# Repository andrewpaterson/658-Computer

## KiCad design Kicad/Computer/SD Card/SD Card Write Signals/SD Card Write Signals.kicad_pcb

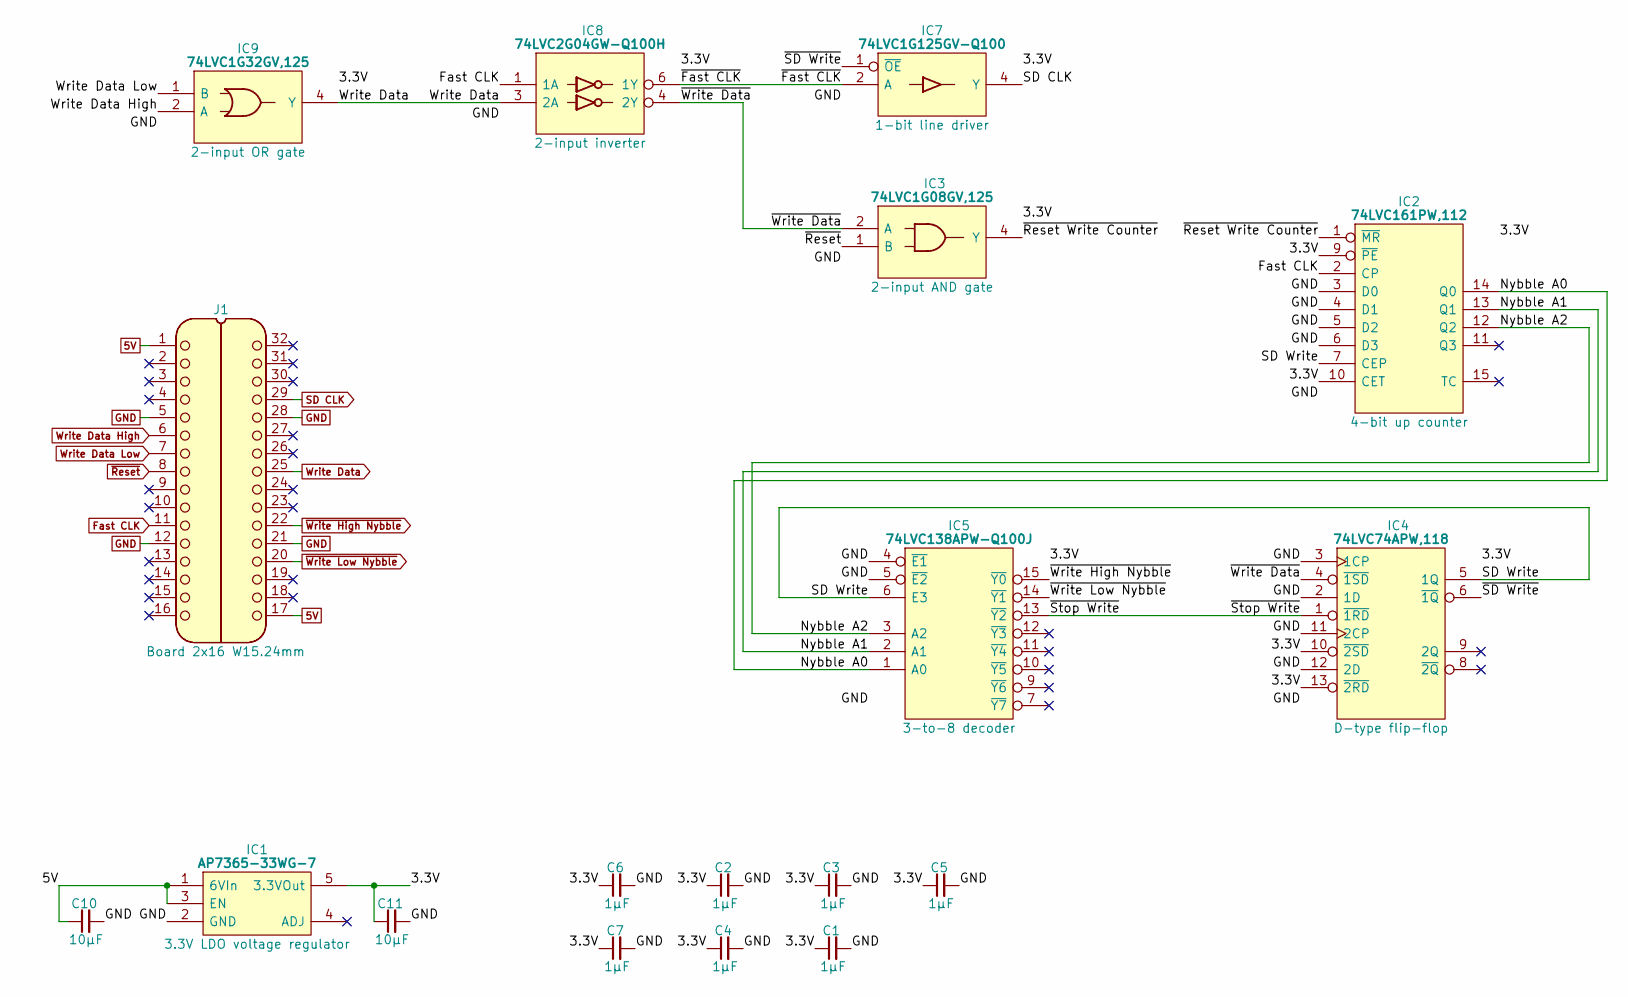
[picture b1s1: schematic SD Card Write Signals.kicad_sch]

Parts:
C1, C2, C3, C4, C5, C6, C7: 1μF; C_0805
C10, C11: 10μF; C_0805
IC1: AP7365-33WG-7; SOT95P285X130-5N; Manufacturer_Part_Number AP7365-33WG-7; Mouser Part Number 621-AP7365-33WG-7
IC2: 74LVC161PW,112; SOP65P640X110-16N; Mouser Part Number 771-LVC161PW112
IC3: 74LVC1G08GV,125; SOT95P275X110-5N; Manufacturer_Part_Number 74LVC1G08GV,125; Mouser Part Number 771-74LVC1G08GV
IC4: 74LVC74APW,118; SOP65P640X110-14N; Mouser Part Number 771-74LVC74APW-T
IC5: 74LVC138APW-Q100J; SOP65P640X110-16N; Mouser Part Number 771-74LVC138APWQ100J
IC7: 74LVC1G125GV-Q100; SOT95P275X110-5N; Mouser Part Number 771-74LVC1G125GVQ100
IC8: 74LVC2G04GW-Q100H; SOP65P210X110-6N; Manufacturer_Part_Number 74LVC2G04GW-Q100H; Mouser Part Number 771-74LVC2G04GWQ100H
IC9: 74LVC1G32GV,125; SOT95P275X110-5N; Manufacturer_Part_Number 74LVC1G32GV,125; Mouser Part Number 771-LVC1G32GV125
J1: Board 2x16 W15.24mm; DIP-32_Board_W15.24mm

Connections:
5V: C10.1, IC1.1 (6VIn), IC1.3 (EN), J1.1, J1.17
/3.3V: C1.1, C2.1, C3.1, C4.1, C5.1, C6.1, C7.1, C11.1, IC1.5 (3.3VOut), IC2.9 (~PE), IC2.10 (CET), IC2.16 (3V), IC3.5 (3V), IC4.10 (~2SD), IC4.13 (~2RD), IC4.14 (3V), IC5.16 (3V), IC7.5 (3V), IC8.5 (3V), IC9.5 (3V)
/Nybble A0: IC2.14 (Q0), IC5.1 (A0)
/Nybble A1: IC2.13 (Q1), IC5.2 (A1)
/Nybble A2: IC2.12 (Q2), IC5.3 (A2)
/SD Write: IC2.7 (CEP), IC4.5 (1Q), IC5.6 (E3)
/~Fast CLK: IC7.2 (A), IC8.6 (1Y)
/~Reset Write Counter: IC2.1 (~MR), IC3.4 (Y)
/~SD Write: IC4.6 (~1Q), IC7.1 (~OE)
/~Stop Write: IC4.1 (~1RD), IC5.13 (~Y2)
/~Write Data: IC3.2 (A), IC4.4 (~1SD), IC8.4 (2Y)
Fast CLK: IC2.2 (CP), IC8.1 (1A), J1.11
GND: C1.2, C2.2, C3.2, C4.2, C5.2, C6.2, C7.2, C10.2, C11.2, IC1.2 (GND), IC2.3 (D0), IC2.4 (D1), IC2.5 (D2), IC2.6 (D3), IC2.8 (GND), IC3.3 (GND), IC4.2 (1D), IC4.3 (1CP), IC4.7 (GND), IC4.11 (2CP), IC4.12 (2D), IC5.4 (~E1), IC5.5 (~E2), IC5.8 (GND), IC7.3 (GND), IC8.2 (GND), IC9.3 (GND), J1.5, J1.12, J1.21, J1.28
SD CLK: IC7.4 (Y), J1.29
Write Data: IC8.3 (2A), IC9.4 (Y), J1.25
Write Data High: IC9.2 (A), J1.6
Write Data Low: IC9.1 (B), J1.7
~Reset: IC3.1 (B), J1.8
~Write High Nybble: IC5.15 (~Y0), J1.22
~Write Low Nybble: IC5.14 (~Y1), J1.20

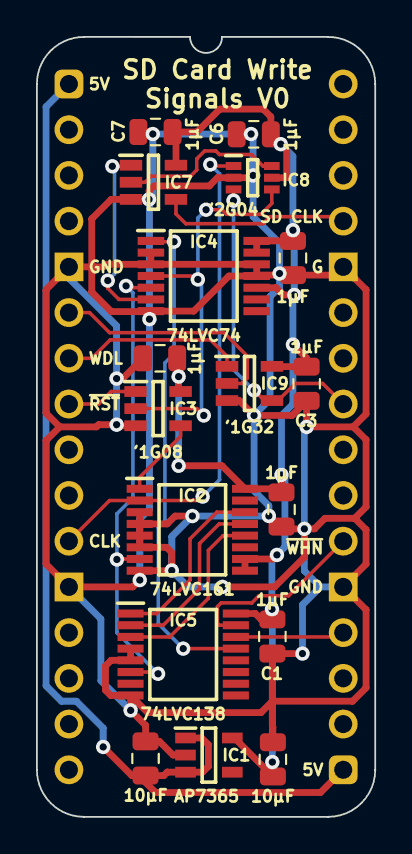
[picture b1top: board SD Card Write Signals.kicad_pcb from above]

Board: 2 copper layers, 18.8 x 43.3 mm, 18 parts (0 on the bottom side), 20 nets.

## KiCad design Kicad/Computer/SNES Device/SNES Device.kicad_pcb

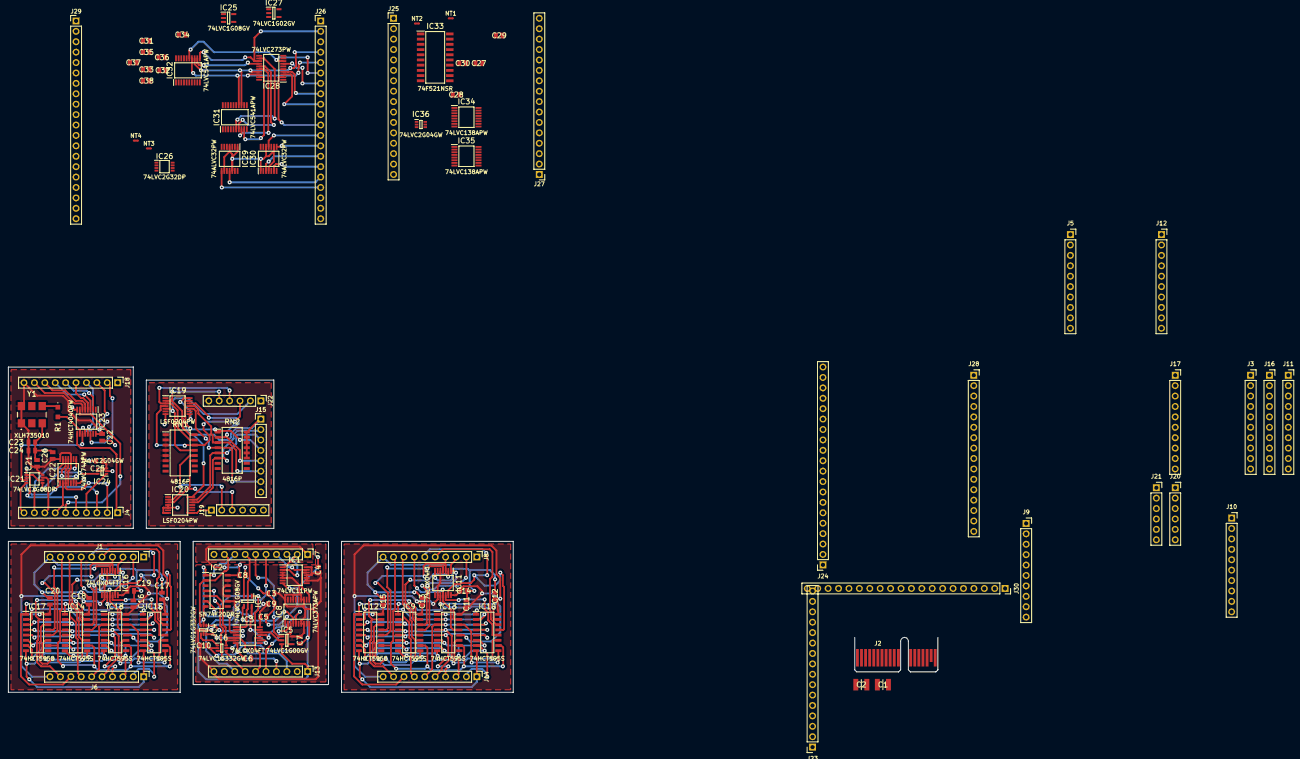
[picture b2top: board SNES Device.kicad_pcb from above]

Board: 2 copper layers, 112 parts (0 on the bottom side), 255 nets.

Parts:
C1, C2: LMK325ABJ107MM-T; CAPC3226X280N
C3, C4, C5, C6, C7, C8, C9, C10, C11, C12, C13, C14, C15, C16, C17, C18, C19, C20, C21, C22, C24, C25, C26, C27, C28, C29, C30, C31, C32, C33, C34, C35, C36, C37, C38: 885012207033; CAPC2012X90N
C23: 885012207027; CAPC2012X90N
IC1: 74LVC11PW,112; SOP65P640X110-14N
IC2: SN74F20DR; SOIC127P600X175-14N
IC3, IC11, IC16: 74LCX04FT_AE_; SOP65P640X120-14N
IC4, IC6: 74LVC1G332GW-Q100H; SOP65P210X110-6N
IC5: 74LVC1G00GV,125; SOT95P275X110-5N
IC7, IC25: 74LVC1G08GV,125; SOT95P275X110-5N
IC8: 74LVC373APW,118; SOP65P640X110-20N
IC9, IC10, IC12, IC13, IC14, IC15, IC17, IC18: 74HCT595S16-13; SOIC127P600X175-16N
IC19, IC20: LSF0204PW-Q100J; SOP65P640X110-14N
IC21: 74LVC2G08DP-Q100H; SOP65P400X110-8N
IC22: 74LVC74APW,118; SOP65P640X110-14N
IC23: 74HCT4040PW,118; SOP65P640X110-16N
IC24, IC36: 74LVC2G04GW-Q100H; SOP65P210X110-6N
IC26: 74LVC2G32DP,125; SOP65P400X110-8N
IC27: 74LVC1G02GV,125; SOT95P275X110-5N
IC28: 74LVC273PW,118; SOP65P640X110-20N
IC29, IC30: 74ALVC32PW,118; SOP65P640X110-14N
IC31, IC32: 74LVC541APW,118; SOP65P640X110-20N
IC33: SN74F521NSR; SOIC127P780X200-20N
IC34, IC35: 74LVC138APW-Q100J; SOP65P640X110-16N
J1, J4, J6, J7, J8, J13, J14, J18: Conn_01x10_Male; PinHeader_1x10_P2.54mm_Vertical
J2: HCP65_PCI_Express_x36_pin; BUS_PCIexpress_x1
J3, J5, J9, J10, J11, J12, J16, J17: Conn_02x05_Top_Bottom; PinSocket_1x10_P2.54mm_Vertical
J15: Conn_01x08_Male; PinHeader_1x08_P2.54mm_Vertical
J19, J22: Conn_01x06_Male; PinHeader_1x06_P2.54mm_Vertical
J20, J21: Conn_02x03_Top_Bottom; PinSocket_1x06_P2.54mm_Vertical
J23, J28: Conn_01x16_Female; PinSocket_1x16_P2.54mm_Vertical
J24, J30: Conn_01x20_Female; PinSocket_1x20_P2.54mm_Vertical
J25, J27: Conn_01x16_Male; PinHeader_1x16_P2.54mm_Vertical
J26, J29: Conn_01x20_Male; PinHeader_1x20_P2.54mm_Vertical
NT1, NT2, NT3, NT4: NetTie_2; NetTie-2_SMD_Pad0.5mm
R1: ERJ-P06F49R9V; ERJP06__0805_
RN1, RN2: 4816P-1-222LF; SOIC127P762X215-16N
Y1: XLH735010.000000X; XLH735010000000X

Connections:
/3.3V: C2.2, J2.B8 (+3.3V), J2.B10 (+3.3V), J5.10, J11.10, J12.10, J17.10, J21.6, J28.16, J30.20
/5V: C1.1, J2.B1 (+5V), J10.1, J20.3, J23.1
/Address0: J2.B12 (Address0), J23.11
/Address1: J2.B13 (Address1), J23.12
/Address2: J2.B14 (Address2), J23.13
/Address3: J2.B15 (Address3), J23.14
/Data0: J2.A3 (Data0), J5.9, J12.9, J30.9
/Data1: J2.A4 (Data1), J5.8, J12.8, J30.8
/Data2: J2.A5 (Data2), J5.7, J12.7, J30.7
/Data3: J2.A6 (Data3), J5.6, J12.6, J30.6
/Data4: J2.A7 (Data4), J5.5, J12.5, J30.5
/Data5: J2.A8 (Data5), J5.4, J12.4, J30.4
/Data6: J2.A9 (Data6), J5.3, J12.3, J30.3
/Data7: J2.A10 (Data7), J5.2, J12.2, J30.2
/GND: C1.2, C2.1, J2.B4 (GND), J3.10, J5.1, J9.10, J10.10, J11.1, J12.1, J16.10, J17.1, J20.6, J21.1, J23.16, J24.20, J28.1, J30.1
/Identifier0: J2.B2 (Identifier0), J23.3
/Identifier1: J2.B3 (Identifier1), J23.4
/Identifier2: J2.B5 (Identifier2), J23.5
/Identifier3: J2.B6 (Identifier3), J23.6
/Identifier4: J2.B7 (Identifier4), J23.7
/Identifier5: J2.B9 (Identifier5), J23.8
/SNES Controller Board/COUNTER_IN0: IC1.1 (1A), J7.2
/SNES Controller Board/COUNTER_IN1: IC1.2 (1B), J7.3
/SNES Controller Board/COUNTER_IN2: IC1.13 (1C), J7.4
/SNES Controller Board/COUNTER_IN3: J7.5, J13.8
/SNES Controller Board/COUNTER_IN4: IC5.1 (B), J7.6
/SNES Controller Board/COUNTER_IN5: IC3.1 (1A), IC7.2 (A), J7.7
/SNES Controller Board/COUNTER_IN6: IC2.1 (1A), IC3.3 (2A), J7.8
/SNES Controller Board/COUNTER_IN7: IC2.2 (1B), IC4.3 (B), J7.9
/SNES Controller Board/COUNTER_IN8: IC2.4 (1C), IC6.3 (B), J13.4
/SNES Controller Board/COUNTER_IN9: IC2.5 (1D), IC3.5 (3A), J13.3
/SNES Controller Board/COUNTER_OUT0: IC23.9 (Q0), J4.1
/SNES Controller Board/COUNTER_OUT1: IC23.7 (Q1), J4.6
/SNES Controller Board/COUNTER_OUT2: IC23.6 (Q2), J18.9
/SNES Controller Board/COUNTER_OUT3: IC23.5 (Q3), J18.8
/SNES Controller Board/COUNTER_OUT4: IC23.3 (Q4), J18.7
/SNES Controller Board/COUNTER_OUT5: IC23.2 (Q5), J18.6
/SNES Controller Board/COUNTER_OUT6: IC23.4 (Q6), J18.5
/SNES Controller Board/COUNTER_OUT7: IC23.13 (Q7), J18.4
/SNES Controller Board/COUNTER_OUT8: IC23.12 (Q8), J18.3
/SNES Controller Board/COUNTER_OUT9: IC23.14 (Q9), J18.2
/SNES Controller Board/COUNTER_VALUE0: J10.2, J16.1
/SNES Controller Board/COUNTER_VALUE1: J10.3, J16.6
/SNES Controller Board/COUNTER_VALUE2: J10.4, J17.9
/SNES Controller Board/COUNTER_VALUE3: J10.5, J17.8
/SNES Controller Board/COUNTER_VALUE4: J10.6, J17.7
/SNES Controller Board/COUNTER_VALUE5: J10.7, J17.6
/SNES Controller Board/COUNTER_VALUE6: J10.8, J17.5
/SNES Controller Board/COUNTER_VALUE7: J10.9, J17.4
/SNES Controller Board/COUNTER_VALUE8: J11.4, J17.3
/SNES Controller Board/COUNTER_VALUE9: J11.3, J17.2
/SNES Controller Board/Controller A Data: J3.2, J21.5
/SNES Controller Board/Controller A ~OE High Byte: J3.4, J30.18
/SNES Controller Board/Controller A ~OE Low Byte: J3.3, J30.19
/SNES Controller Board/Controller B Data: J3.5, J21.4
/SNES Controller Board/Controller B ~OE High Byte: J3.7, J30.16
/SNES Controller Board/Controller B ~OE Low Byte: J3.6, J30.17
/SNES Controller Board/Controller C Data: J9.2, J21.3
/SNES Controller Board/Controller C ~OE High Byte: J9.4, J30.14
/SNES Controller Board/Controller C ~OE Low Byte: J9.3, J30.15
/SNES Controller Board/Controller Clock: J11.5, J16.7, J20.2
/SNES Controller Board/Controller D Data: J9.5, J21.2
/SNES Controller Board/Controller D ~OE High Byte: J9.7, J30.12
/SNES Controller Board/Controller D ~OE Low Byte: J9.6, J30.13
/SNES Controller Board/Controller Latch: J11.6, J16.5, J20.1
/SNES Controller Board/Counter 3.3V: C21.1, C22.1, C23.1, C24.1, C25.1, C26.1, IC21.8 (VCC), IC22.4 (~1SD), IC22.10 (~2SD), IC22.14 (VCC), IC23.16 (VCC), IC24.3 (2A), IC24.5 (VCC), J18.10, Y1.1 (E/D_/_NC), Y1.6 (VDD)
/SNES Controller Board/Counter GND: C21.2, C22.2, C23.2, C24.2, C25.2, C26.2, IC21.4 (GND), IC22.7 (GND), IC23.8 (GND), IC24.2 (GND), J4.10, J18.1, Y1.3 (GND)
/SNES Controller Board/Counter Reset: J16.4, J30.11
/SNES Controller Board/J5_5: IC8.2 (Q0), J13.5
/SNES Controller Board/J5_6: IC3.10 (5Y), J13.6
/SNES Controller Board/J5_7: IC6.4 (Y), J13.7
/SNES Controller Board/Pre-Clock: J11.8, J16.2
/SNES Controller Board/SNES Controller Counter/Controller Clock: IC22.2 (1D), J4.7
/SNES Controller Board/SNES Controller Counter/Controller Latch: IC21.2 (1B), J4.5
/SNES Controller Board/SNES Controller Counter/Counter Reset: IC24.1 (1A), J4.4
/SNES Controller Board/SNES Controller Counter/HCT4040 MR: IC21.3 (2Y), IC23.11 (MR)
/SNES Controller Board/SNES Controller Counter/Pre-Clock: IC22.3 (1CP), IC22.11 (2CP), J4.2
/SNES Controller Board/SNES Controller Counter/Shift Clock: IC22.8 (~2Q), J4.9
/SNES Controller Board/SNES Controller Counter/~Reset: IC21.1 (1A), IC21.6 (2B), IC22.1 (~1RD), IC22.13 (~2RD), J4.3
/SNES Controller Board/SNES Controller Counter/~Shift Reset: IC21.7 (1Y), J4.8
/SNES Controller Board/SNES Controller Shift Register1/3.3V: C16.1, C17.1, C18.1, C19.1, C20.1, IC14.16 (VCC), IC15.16 (VCC), IC16.5 (3A), IC16.9 (4A), IC16.14 (VCC), IC17.16 (VCC), IC18.16 (VCC), J6.10
/SNES Controller Board/SNES Controller Shift Register1/Controller A Data: IC14.14 (DS), J1.2
/SNES Controller Board/SNES Controller Shift Register1/Controller A ~OE High By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: IC16.3 (2A), IC17.13 (~OE), J1.4
/SNES Controller Board/SNES Controller Shift Register1/Controller A ~OE Low Byte: IC14.13 (~OE), IC16.1 (1A), J1.3
/SNES Controller Board/SNES Controller Shift Register1/Controller B Data: IC15.14 (DS), J1.5
/SNES Controller Board/SNES Controller Shift Register1/Controller B ~OE High By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: IC16.11 (5A), IC18.13 (~OE), J1.7
/SNES Controller Board/SNES Controller Shift Register1/Controller B ~OE Low Byte: IC15.13 (~OE), IC16.13 (6A), J1.6
/SNES Controller Board/SNES Controller Shift Register1/GND: C16.2, C17.2, C18.2, C19.2, C20.2, IC14.8 (GND), IC15.8 (GND), IC16.7 (GND), IC17.8 (GND), IC18.8 (GND), J1.10, J6.1
/SNES Controller Board/SNES Controller Shift Register1/SHIFT_OUT0: IC14.15 (Q0), IC15.15 (Q0), IC17.15 (Q0), IC18.15 (Q0), J6.9
/SNES Controller Board/SNES Controller Shift Register1/SHIFT_OUT1: IC14.1 (Q1), IC15.1 (Q1), IC17.1 (Q1), IC18.1 (Q1), J6.8
/SNES Controller Board/SNES Controller Shift Register1/SHIFT_OUT2: IC14.2 (Q2), IC15.2 (Q2), IC17.2 (Q2), IC18.2 (Q2), J6.7
/SNES Controller Board/SNES Controller Shift Register1/SHIFT_OUT3: IC14.3 (Q3), IC15.3 (Q3), IC17.3 (Q3), IC18.3 (Q3), J6.6
/SNES Controller Board/SNES Controller Shift Register1/SHIFT_OUT4: IC14.4 (Q4), IC15.4 (Q4), IC17.4 (Q4), IC18.4 (Q4), J6.5
/SNES Controller Board/SNES Controller Shift Register1/SHIFT_OUT5: IC14.5 (Q5), IC15.5 (Q5), IC17.5 (Q5), IC18.5 (Q5), J6.4
/SNES Controller Board/SNES Controller Shift Register1/SHIFT_OUT6: IC14.6 (Q6), IC15.6 (Q6), IC17.6 (Q6), IC18.6 (Q6), J6.3
/SNES Controller Board/SNES Controller Shift Register1/SHIFT_OUT7: IC14.7 (Q7), IC15.7 (Q7), IC17.7 (Q7), IC18.7 (Q7), J6.2
/SNES Controller Board/SNES Controller Shift Register1/Shift Clock: IC14.11 (SHCP), IC15.11 (SHCP), IC17.11 (SHCP), IC18.11 (SHCP), J1.8
/SNES Controller Board/SNES Controller Shift Register1/~Shift Reset: IC14.10 (~MR), IC15.10 (~MR), IC17.10 (~MR), IC18.10 (~MR), J1.9
/SNES Controller Board/SNES Controller Shift Register/3.3V: C11.1, C12.1, C13.1, C14.1, C15.1, IC9.16 (VCC), IC10.16 (VCC), IC11.5 (3A), IC11.9 (4A), IC11.14 (VCC), IC12.16 (VCC), IC13.16 (VCC), J14.10
/SNES Controller Board/SNES Controller Shift Register/Controller A Data: IC9.14 (DS), J8.2
/SNES Controller Board/SNES Controller Shift Register/Controller A ~OE High Byte: IC11.3 (2A), IC12.13 (~OE), J8.4
/SNES Controller Board/SNES Controller Shift Register/Controller A ~OE Low Byte: IC9.13 (~OE), IC11.1 (1A), J8.3
/SNES Controller Board/SNES Controller Shift Register/Controller B Data: IC10.14 (DS), J8.5
/SNES Controller Board/SNES Controller Shift Register/Controller B ~OE High Byte: IC11.11 (5A), IC13.13 (~OE), J8.7
/SNES Controller Board/SNES Controller Shift Register/Controller B ~OE Low Byte: IC10.13 (~OE), IC11.13 (6A), J8.6
/SNES Controller Board/SNES Controller Shift Register/GND: C11.2, C12.2, C13.2, C14.2, C15.2, IC9.8 (GND), IC10.8 (GND), IC11.7 (GND), IC12.8 (GND), IC13.8 (GND), J8.10, J14.1
/SNES Controller Board/SNES Controller Shift Register/SHIFT_OUT0: IC9.15 (Q0), IC10.15 (Q0), IC12.15 (Q0), IC13.15 (Q0), J14.9
/SNES Controller Board/SNES Controller Shift Register/SHIFT_OUT1: IC9.1 (Q1), IC10.1 (Q1), IC12.1 (Q1), IC13.1 (Q1), J14.8
/SNES Controller Board/SNES Controller Shift Register/SHIFT_OUT2: IC9.2 (Q2), IC10.2 (Q2), IC12.2 (Q2), IC13.2 (Q2), J14.7
/SNES Controller Board/SNES Controller Shift Register/SHIFT_OUT3: IC9.3 (Q3), IC10.3 (Q3), IC12.3 (Q3), IC13.3 (Q3), J14.6
/SNES Controller Board/SNES Controller Shift Register/SHIFT_OUT4: IC9.4 (Q4), IC10.4 (Q4), IC12.4 (Q4), IC13.4 (Q4), J14.5
/SNES Controller Board/SNES Controller Shift Register/SHIFT_OUT5: IC9.5 (Q5), IC10.5 (Q5), IC12.5 (Q5), IC13.5 (Q5), J14.4
/SNES Controller Board/SNES Controller Shift Register/SHIFT_OUT6: IC9.6 (Q6), IC10.6 (Q6), IC12.6 (Q6), IC13.6 (Q6), J14.3
/SNES Controller Board/SNES Controller Shift Register/SHIFT_OUT7: IC9.7 (Q7), IC10.7 (Q7), IC12.7 (Q7), IC13.7 (Q7), J14.2
/SNES Controller Board/SNES Controller Shift Register/Shift Clock: IC9.11 (SHCP), IC10.11 (SHCP), IC12.11 (SHCP), IC13.11 (SHCP), J8.8
/SNES Controller Board/SNES Controller Shift Register/~Shift Reset: IC9.10 (~MR), IC10.10 (~MR), IC12.10 (~MR), IC13.10 (~MR), J8.9
/SNES Controller Board/SNES Controller Timing/LE: IC1.12 (1Y), IC8.11 (LE)
/SNES Controller Board/SNES Controller Translation/3.3V: IC19.1 (REFA), IC20.1 (REFA), J22.6, RN1.1 (R1_1), RN1.2 (R2_1), RN1.3 (R3_1), RN1.4 (R4_1), RN1.5 (R5_1), RN1.6 (R6_1)
/SNES Controller Board/SNES Controller Translation/5V: IC19.8 (EN), IC19.14 (REFB), IC20.8 (EN), IC20.14 (REFB), J15.1, J19.1, RN2.11 (R6_2), RN2.12 (R5_2), RN2.13 (R4_2), RN2.14 (R3_2), RN2.15 (R2_2), RN2.16 (R1_2)
/SNES Controller Board/SNES Controller Translation/Controller A Data: IC19.2 (A1), J22.5, RN1.16 (R1_2)
/SNES Controller Board/SNES Controller Translation/Controller B Data: IC19.3 (A2), J22.4, RN1.15 (R2_2)
/SNES Controller Board/SNES Controller Translation/Controller C Data: IC19.4 (A3), J22.3, RN1.14 (R3_2)
/SNES Controller Board/SNES Controller Translation/Controller Clock: IC20.3 (A2), J19.3, RN1.11 (R6_2)
/SNES Controller Board/SNES Controller Translation/Controller D Data: IC19.5 (A4), J22.2, RN1.13 (R4_2)
/SNES Controller Board/SNES Controller Translation/Controller Latch: IC20.2 (A1), J19.2, RN1.12 (R5_2)
/SNES Controller Board/SNES Controller Translation/GND: IC19.7 (GND), IC20.4 (A3), IC20.5 (A4), IC20.7 (GND), J15.8, J19.6, J22.1
/SNES Controller Board/Shift Clock: J3.8, J9.8, J16.9
/SNES Controller Board/Timing 3.3V: C3.1, C4.1, C5.1, C6.1, C7.1, C9.1, C10.1, IC1.3 (2A), IC1.4 (2B), IC1.5 (2C), IC1.9 (3A), IC1.10 (3B), IC1.11 (3C), IC1.14 (VCC), IC2.9 (2A), IC2.10 (2B), IC2.12 (2C), IC2.13 (2D), IC3.9 (4A), IC3.14 (VCC), IC4.5 (VCC), IC5.5 (VCC), IC6.5 (VCC), IC7.5 (VCC), IC8.7 (D2), IC8.8 (D3), IC8.13 (D4), IC8.14 (D5), IC8.17 (D6), IC8.18 (D7), IC8.20 (VCC), J13.10
/SNES Controller Board/Timing 5V: C8.1, IC2.14 (VCC), J7.1
/SNES Controller Board/Timing GND: C3.2, C4.2, C5.2, C6.2, C7.2, C8.2, C9.2, C10.2, IC1.7 (GND), IC2.7 (GND), IC3.7 (GND), IC4.2 (GND), IC5.3 (GND), IC6.2 (GND), IC7.3 (GND), IC8.1 (~OE), IC8.10 (GND), J7.10, J13.1
/SNES Controller Board/~Done Shifting: J11.7, J24.16
/SNES Controller Board/~Reset: J2.B11 (~Reset), J16.3, J24.17
/SNES Controller Board/~Shift Reset: J3.9, J9.9, J16.8
/SNES Controller Device/Channel RWB: IC26.1 (1A), J29.18
/SNES Controller Device/Channel ~RWB: IC26.5 (2A), J29.19
/SNES Controller Device/Device Channel RWB: J2.A2 (RWB), J24.18
/SNES Controller Device/Device Channel ~RWB: J2.A11 (~RWB), J24.19
/SNES Controller Device/Device Selector/DEVICE_ADDRESS0: IC34.1 (A0), IC35.1 (A0), J25.11
/SNES Controller Device/Device Selector/DEVICE_ADDRESS1: IC34.2 (A1), IC35.2 (A1), J25.12
/SNES Controller Device/Device Selector/DEVICE_ADDRESS2: IC34.3 (A2), IC35.3 (A2), J25.13
/SNES Controller Device/Device Selector/DEVICE_ADDRESS3: IC34.4 (~E1), IC34.5 (~E2), IC35.6 (E3), J25.14
/SNES Controller Device/Device Selector/DEVICE_IDENTIFIER0: IC33.2 (P0), J25.3
/SNES Controller Device/Device Selector/DEVICE_IDENTIFIER1: IC33.4 (P1), J25.4
/SNES Controller Device/Device Selector/DEVICE_IDENTIFIER2: IC33.6 (P2), J25.5
/SNES Controller Device/Device Selector/DEVICE_IDENTIFIER3: IC33.8 (P3), J25.6
/SNES Controller Device/Device Selector/DEVICE_IDENTIFIER4: IC33.11 (P4), J25.7
/SNES Controller Device/Device Selector/DEVICE_IDENTIFIER5: IC33.13 (P5), J25.8
/SNES Controller Device/Device Selector/HARD_IDENTIFIER0: IC33.3 (Q0), IC33.12 (Q4), IC33.14 (Q5), NT2.2
/SNES Controller Device/Device Selector/HARD_IDENTIFIER3: IC33.5 (Q1), IC33.7 (Q2), IC33.9 (Q3), NT1.2
/SNES Controller Device/Left 3.3V: C27.1, C29.1, C30.1, IC34.6 (E3), IC34.16 (VCC), IC35.16 (VCC), IC36.5 (VCC), J27.16, NT1.1
/SNES Controller Device/Left 5V: C28.1, IC33.20 (VCC), J25.1
/SNES Controller Device/Left GND: C27.2, C28.2, C29.2, C30.2, IC33.1 (~OE), IC33.10 (GND), IC33.15 (P6), IC33.16 (Q6), IC33.17 (P7), IC33.18 (Q7), IC34.8 (GND), IC35.4 (~E1), IC35.5 (~E2), IC35.8 (GND), IC36.2 (GND), IC36.3 (2A), J25.16, J27.1, NT2.1
/SNES Controller Device/Right 3.3V: C31.1, C32.1, C33.1, C34.1, C35.1, C36.1, C37.1, C38.1, IC25.5 (VCC), IC26.8 (VCC), IC27.5 (VCC), IC28.20 (VCC), IC29.14 (VCC), IC30.14 (VCC), IC31.20 (VCC), IC32.20 (VCC), J26.20, NT3.1
/SNES Controller Device/Right GND: C31.2, C32.2, C33.2, C34.2, C35.2, C36.2, C37.2, C38.2, IC25.3 (GND), IC26.4 (GND), IC27.3 (GND), IC28.10 (GND), IC29.7 (GND), IC30.7 (GND), IC31.10 (GND), IC32.10 (GND), J26.1, J29.20, NT4.1
/SNES Controller Device/SNES Device Selector/Controller A ~OE High Byte: IC29.3 (1Y), J26.18
/SNES Controller Device/SNES Device Selector/Controller A ~OE Low Byte: IC29.6 (2Y), J26.19
/SNES Controller Device/SNES Device Selector/Controller B ~OE High Byte: IC29.11 (4Y), J26.16
/SNES Controller Device/SNES Device Selector/Controller B ~OE Low Byte: IC29.8 (3Y), J26.17
/SNES Controller Device/SNES Device Selector/Controller C ~OE High Byte: IC30.3 (1Y), J26.14
/SNES Controller Device/SNES Device Selector/Controller C ~OE Low Byte: IC30.6 (2Y), J26.15
/SNES Controller Device/SNES Device Selector/Controller D ~OE High Byte: IC30.11 (4Y), J26.12
/SNES Controller Device/SNES Device Selector/Controller D ~OE Low Byte: IC30.8 (3Y), J26.13
/SNES Controller Device/SNES Device Selector/Counter Reset: IC28.2 (Q0), IC31.2 (A0), J26.11
/SNES Controller Device/SNES Device Selector/Data0: IC28.3 (D0), IC31.18 (Y0), IC32.18 (Y0), J26.9
/SNES Controller Device/SNES Device Selector/Data1: IC28.4 (D1), IC31.17 (Y1), IC32.17 (Y1), J26.8
/SNES Controller Device/SNES Device Selector/Data2: IC28.7 (D2), IC31.16 (Y2), IC32.16 (Y2), J26.7
/SNES Controller Device/SNES Device Selector/Data3: IC28.8 (D3), IC31.15 (Y3), IC32.15 (Y3), J26.6
/SNES Controller Device/SNES Device Selector/Data4: IC28.18 (D7), IC31.14 (Y4), IC32.14 (Y4), J26.5
/SNES Controller Device/SNES Device Selector/Data5: IC28.17 (D6), IC31.13 (Y5), IC32.13 (Y5), J26.4
/SNES Controller Device/SNES Device Selector/Data6: IC28.14 (D5), IC31.12 (Y6), IC32.12 (Y6), J26.3
/SNES Controller Device/SNES Device Selector/Data7: IC28.13 (D4), IC31.11 (Y7), IC32.11 (Y7), J26.2
/SNES Controller Device/SNES Device Selector/Presence3: IC32.2 (A0), IC32.3 (A1), IC32.4 (A2), IC32.5 (A3), IC32.8 (A6), NT4.2
/SNES Controller Device/SNES Device Selector/Presence7: IC32.6 (A4), IC32.7 (A5), IC32.9 (A7), NT3.2
/SNES Controller Device/SNES Device Selector/Read + ~Device: IC26.3 (2Y), IC27.1 (B), IC31.1 (~OE1), IC32.1 (~OE1)
/SNES Controller Device/SNES Device Selector/Write + ~Device: IC26.7 (1Y), IC29.1 (1A), IC29.4 (2A), IC29.9 (3A), IC29.12 (4A), IC30.1 (1A), IC30.4 (2A), IC30.9 (3A), IC30.12 (4A)
/SNES Controller Device/Select In 0: IC32.19 (~OE2), J29.3
/SNES Controller Device/Select In 2: IC27.2 (A), IC31.19 (~OE2), J29.5
/SNES Controller Device/Select In 4: IC29.2 (1B), J29.7
/SNES Controller Device/Select In 5: IC29.5 (2B), J29.8
/SNES Controller Device/Select In 6: IC29.10 (3B), J29.9
/SNES Controller Device/Select In 7: IC29.13 (4B), J29.10
/SNES Controller Device/Select In 8: IC30.2 (1B), J29.11
/SNES Controller Device/Select In 9: IC30.5 (2B), J29.12
/SNES Controller Device/Select In 10: IC30.10 (3B), J29.13
/SNES Controller Device/Select In 11: IC30.13 (4B), J29.14
/SNES Controller Device/Select Out 0: IC34.15 (~Y0), J27.13
/SNES Controller Device/Select Out 1: IC34.14 (~Y1), J27.12
/SNES Controller Device/Select Out 2: IC34.13 (~Y2), J27.11
/SNES Controller Device/Select Out 3: IC34.12 (~Y3), J27.10
/SNES Controller Device/Select Out 4: IC34.11 (~Y4), J27.9
/SNES Controller Device/Select Out 5: IC34.10 (~Y5), J27.8
/SNES Controller Device/Select Out 6: IC34.9 (~Y6), J27.7
/SNES Controller Device/Select Out 7: IC34.7 (~Y7), J27.6
/SNES Controller Device/Select Out 8: IC35.15 (~Y0), J27.5
/SNES Controller Device/Select Out 9: IC35.14 (~Y1), J27.4
/SNES Controller Device/Select Out 10: IC35.13 (~Y2), J27.3
/SNES Controller Device/Select Out 11: IC35.12 (~Y3), J27.2
/SNES Controller Device/Selected: IC36.6 (1Y), J27.15
/SNES Controller Device/~Latch Reset: IC25.1 (B), J29.16
/SNES Controller Device/~P=Q In: IC26.2 (1B), IC26.6 (2B), J29.2
/SNES Controller Device/~P=Q Out: IC33.19 (~P=Q), IC36.1 (1A), J27.14
/SNES Controller Device/~Reset: IC25.2 (A), J29.17
unnamed: IC2.6 (1Y), IC3.13 (6A), IC7.1 (B)
unnamed: IC3.2 (1Y), IC4.1 (A)
unnamed: IC3.4 (2Y), IC4.6 (C)
unnamed: IC3.6 (3Y), IC6.6 (C)
unnamed: IC3.11 (5A), IC8.5 (Q1)
unnamed: IC3.12 (6Y), IC5.2 (A)
unnamed: IC4.4 (Y), IC6.1 (A)
unnamed: IC5.4 (Y), IC8.3 (D0)
unnamed: IC7.4 (Y), IC8.4 (D1)
unnamed: IC10.9 (Q7S), IC13.14 (DS)
unnamed: IC10.12 (STCP), IC11.12 (6Y)
unnamed: IC9.12 (STCP), IC11.2 (1Y)
unnamed: IC11.4 (2Y), IC12.12 (STCP)
unnamed: IC11.10 (5Y), IC13.12 (STCP)
unnamed: IC9.9 (Q7S), IC12.14 (DS)
unnamed: IC14.9 (Q7S), IC17.14 (DS)
unnamed: IC14.12 (STCP), IC16.2 (1Y)
unnamed: IC15.9 (Q7S), IC18.14 (DS)
unnamed: IC15.12 (STCP), IC16.12 (6Y)
unnamed: IC16.4 (2Y), IC17.12 (STCP)
unnamed: IC16.10 (5Y), IC18.12 (STCP)
unnamed: IC19.10 (B4), J15.7, RN2.4 (R4_1)
unnamed: IC19.11 (B3), J15.6, RN2.3 (R3_1)
unnamed: IC19.12 (B2), J15.5, RN2.2 (R2_1)
unnamed: IC19.13 (B1), J15.4, RN2.1 (R1_1)
unnamed: IC20.12 (B2), J15.2, RN2.6 (R6_1)
unnamed: IC20.13 (B1), J15.3, RN2.5 (R5_1)
unnamed: IC21.5 (2A), IC24.6 (1Y)
unnamed: IC22.6 (~1Q), IC22.12 (2D)
unnamed: IC23.10 (~CP), R1.2
unnamed: IC25.4 (Y), IC28.1 (~MR)
unnamed: IC27.4 (Y), IC28.11 (CP)
unnamed: IC28.5 (Q1), IC31.3 (A1)
unnamed: IC28.6 (Q2), IC31.4 (A2)
unnamed: IC28.9 (Q3), IC31.5 (A3)
unnamed: IC28.12 (Q4), IC31.6 (A4)
unnamed: IC28.15 (Q5), IC31.7 (A5)
unnamed: IC28.16 (Q6), IC31.8 (A6)
unnamed: IC28.19 (Q7), IC31.9 (A7)
unnamed: J24.2, J28.14
unnamed: J24.3, J28.13
unnamed: J24.4, J28.12
unnamed: J24.5, J28.11
unnamed: J24.6, J28.10
unnamed: J24.7, J28.9
unnamed: J24.8, J28.8
unnamed: J24.9, J28.7
unnamed: J24.10, J28.6
unnamed: J24.11, J28.5
unnamed: J24.12, J28.4
unnamed: J24.13, J28.3
unnamed: J24.14, J28.2
unnamed: R1.1, Y1.4 (OUT)

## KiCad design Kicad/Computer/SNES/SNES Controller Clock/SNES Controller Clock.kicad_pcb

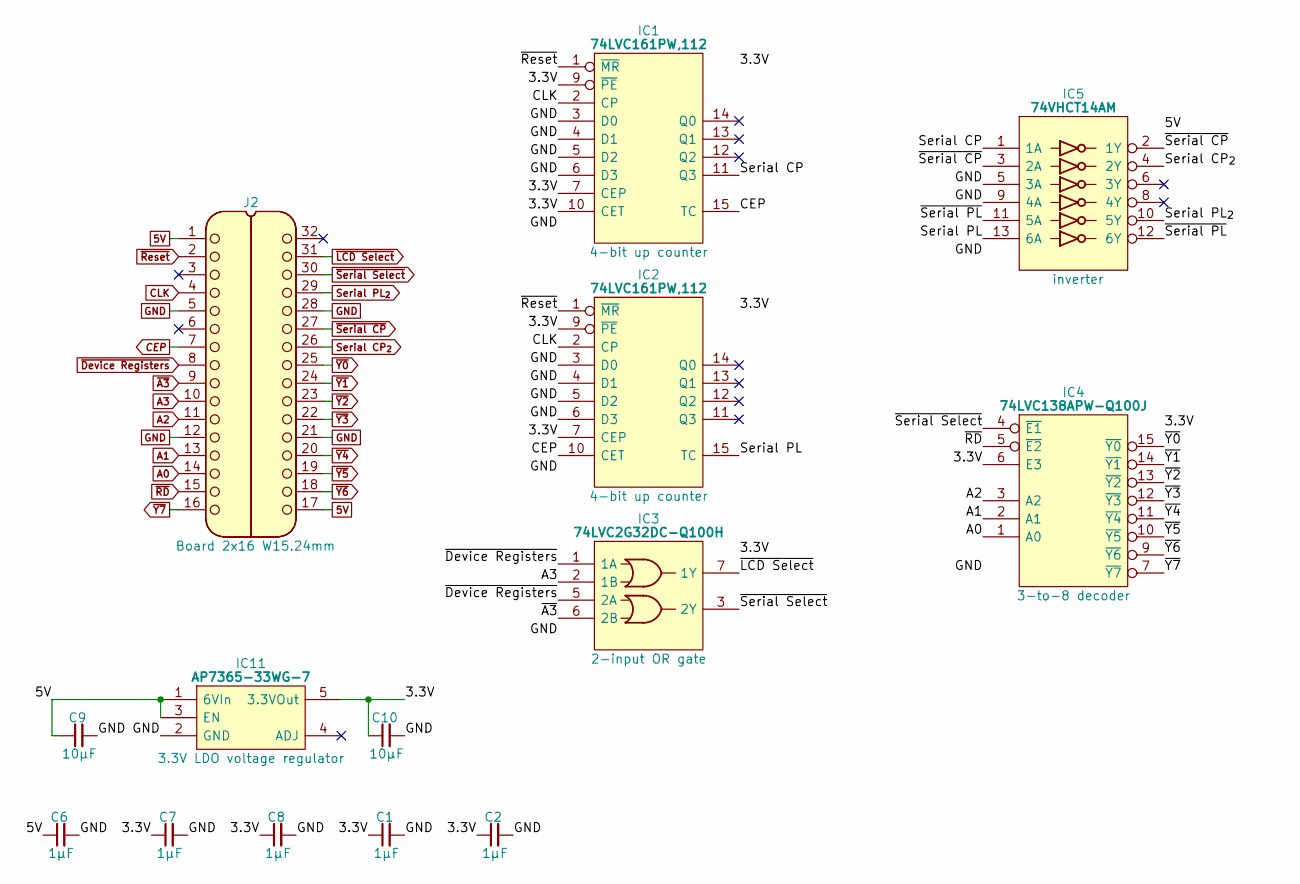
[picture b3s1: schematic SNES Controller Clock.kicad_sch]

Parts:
C1, C2, C6, C7, C8: 1μF; C_0805
C9, C10: 10μF; C_0805
IC1, IC2: 74LVC161PW,112; SOP65P640X110-16N; Mouser Part Number 771-LVC161PW112
IC3: 74LVC2G32DC-Q100H; SOP50P310X100-8N; Mouser Part Number 771-74LVC2G32DCQ100H
IC4: 74LVC138APW-Q100J; SOP65P640X110-16N; Mouser Part Number 771-74LVC138APWQ100J
IC5: 74VHCT14AM; SOIC127P600X175-14N; Manufacturer_Part_Number 74VHCT14AM; Mouser Part Number 512-74VHCT14AM
IC11: AP7365-33WG-7; SOT95P285X130-5N; Manufacturer_Part_Number AP7365-33WG-7; Mouser Part Number 621-AP7365-33WG-7
J2: Board 2x16 W15.24mm; DIP-32_Board_W15.24mm

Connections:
5V: C6.1, C9.1, IC5.14 (5V), IC11.1 (6VIn), IC11.3 (EN), J2.1, J2.17
/3.3V: C1.1, C2.1, C7.1, C8.1, C10.1, IC1.7 (CEP), IC1.9 (~PE), IC1.10 (CET), IC1.16 (3V), IC2.7 (CEP), IC2.9 (~PE), IC2.16 (3V), IC3.8 (VCC), IC4.6 (E3), IC4.16 (3V), IC11.5 (3.3VOut)
/Serial CP: IC1.11 (Q3), IC5.1 (1A)
/Serial PL: IC2.15 (TC), IC5.13 (6A)
/~Serial PL: IC5.11 (5A), IC5.12 (6Y)
A0: IC4.1 (A0), J2.14
A1: IC4.2 (A1), J2.13
A2: IC4.3 (A2), J2.11
A3: IC3.2 (1B), J2.10
CEP: IC1.15 (TC), IC2.10 (CET), J2.7
CLK: IC1.2 (CP), IC2.2 (CP), J2.4
GND: C1.2, C2.2, C6.2, C7.2, C8.2, C9.2, C10.2, IC1.3 (D0), IC1.4 (D1), IC1.5 (D2), IC1.6 (D3), IC1.8 (GND), IC2.3 (D0), IC2.4 (D1), IC2.5 (D2), IC2.6 (D3), IC2.8 (GND), IC3.4 (GND), IC4.8 (GND), IC5.5 (3A), IC5.7 (GND), IC5.9 (4A), IC11.2 (GND), J2.5, J2.12, J2.21, J2.28
Serial CP_{2}: IC5.4 (2Y), J2.26
Serial PL_{2}: IC5.10 (5Y), J2.29
~A3: IC3.6 (2B), J2.9
~Device Registers: IC3.1 (1A), IC3.5 (2A), J2.8
~LCD Select: IC3.7 (1Y), J2.31
~RD: IC4.5 (~E2), J2.15
~Reset: IC1.1 (~MR), IC2.1 (~MR), J2.2
~Serial CP: IC5.2 (1Y), IC5.3 (2A), J2.27
~Serial Select: IC3.3 (2Y), IC4.4 (~E1), J2.30
~Y0: IC4.15 (~Y0), J2.25
~Y1: IC4.14 (~Y1), J2.24
~Y2: IC4.13 (~Y2), J2.23
~Y3: IC4.12 (~Y3), J2.22
~Y4: IC4.11 (~Y4), J2.20
~Y5: IC4.10 (~Y5), J2.19
~Y6: IC4.9 (~Y6), J2.18
~Y7: IC4.7 (~Y7), J2.16

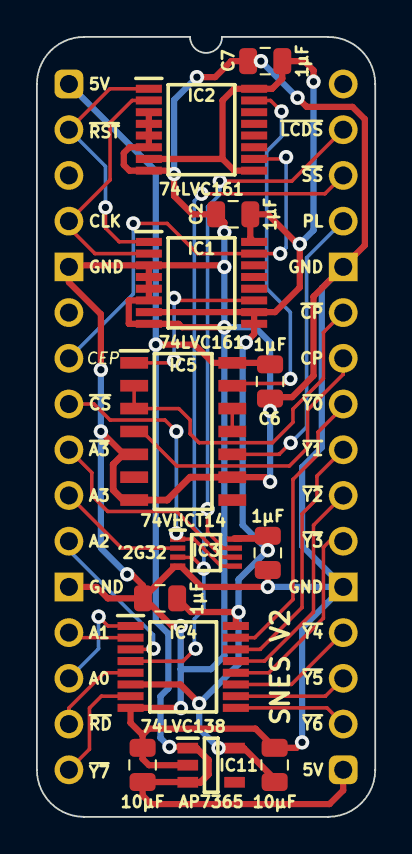
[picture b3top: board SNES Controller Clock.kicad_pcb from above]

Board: 2 copper layers, 18.8 x 43.3 mm, 14 parts (0 on the bottom side), 29 nets.

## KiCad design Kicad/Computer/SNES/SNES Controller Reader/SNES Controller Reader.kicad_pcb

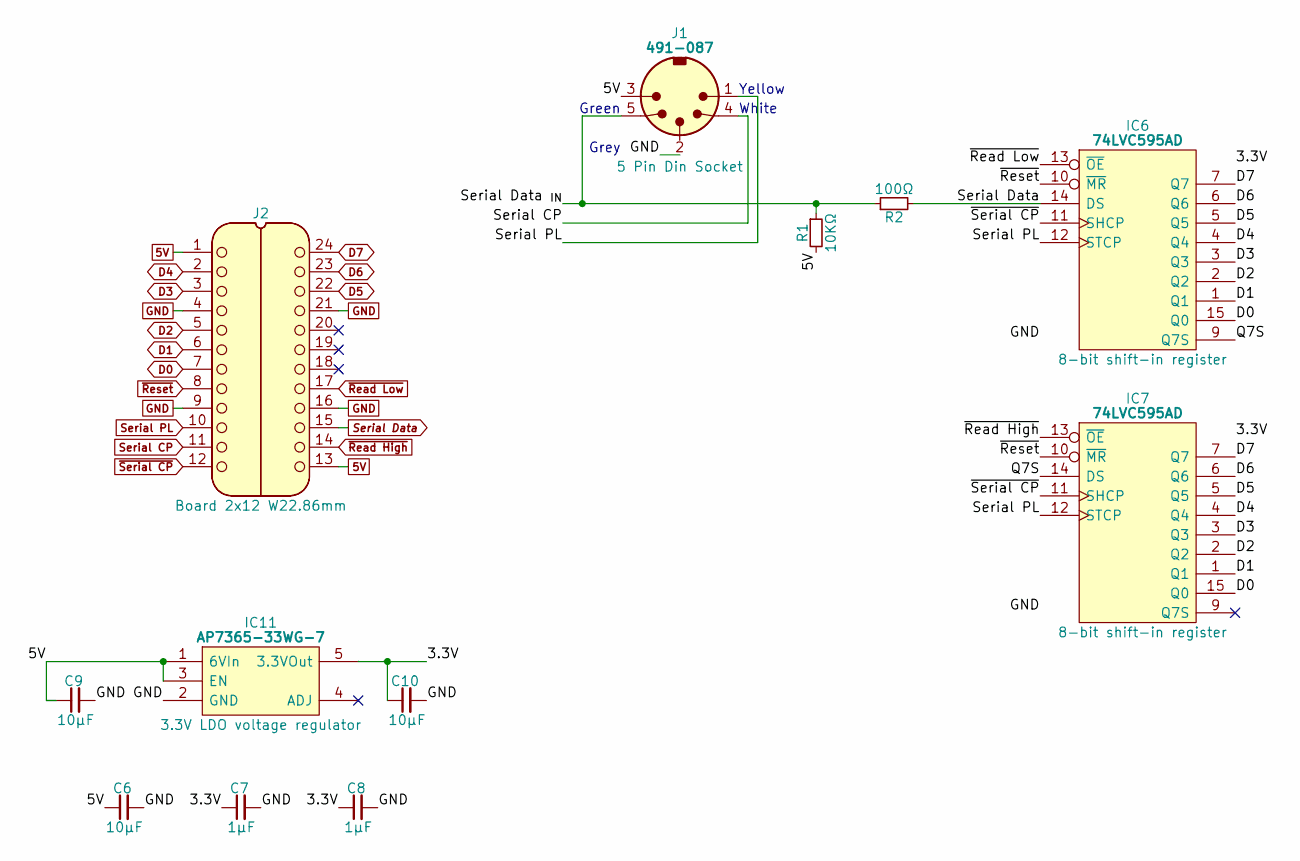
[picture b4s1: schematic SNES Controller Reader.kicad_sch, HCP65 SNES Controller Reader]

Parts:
C6, C9, C10: 10μF; C_0805
C7, C8: 1μF; C_0805
IC6, IC7: 74LVC595AD; SOIC127P600X175-16N; Mouser Part Number 771-74LVC595AD
IC11: AP7365-33WG-7; SOT95P285X130-5N; Manufacturer_Part_Number AP7365-33WG-7; Mouser Part Number 621-AP7365-33WG-7
J1: 491-087; 491087; Manufacturer_Part_Number 491-087
J2: Board 2x12 W22.86mm; DIP-24_Board_W22.86mm
R1: 10KΩ; R_0805
R2: 100Ω; R_0805

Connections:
5V: C6.1, C9.1, IC11.1 (6VIn), IC11.3 (EN), J1.3, J2.1, J2.13, R1.2
/3.3V: C7.1, C8.1, C10.1, IC6.16 (3V), IC7.16 (3V), IC11.5 (3.3VOut)
/Q7S: IC6.9 (Q7S), IC7.14 (DS)
/Serial Data _{IN}: J1.5, R1.1, R2.1
D0: IC6.15 (Q0), IC7.15 (Q0), J2.7
D1: IC6.1 (Q1), IC7.1 (Q1), J2.6
D2: IC6.2 (Q2), IC7.2 (Q2), J2.5
D3: IC6.3 (Q3), IC7.3 (Q3), J2.3
D4: IC6.4 (Q4), IC7.4 (Q4), J2.2
D5: IC6.5 (Q5), IC7.5 (Q5), J2.22
D6: IC6.6 (Q6), IC7.6 (Q6), J2.23
D7: IC6.7 (Q7), IC7.7 (Q7), J2.24
GND: C6.2, C7.2, C8.2, C9.2, C10.2, IC6.8 (GND), IC7.8 (GND), IC11.2 (GND), J1.2, J2.4, J2.9, J2.16, J2.21
Serial CP: J1.4, J2.11
Serial Data: IC6.14 (DS), J2.15, R2.2
Serial PL: IC6.12 (STCP), IC7.12 (STCP), J1.1, J2.10
~Read High: IC7.13 (~OE), J2.14
~Read Low: IC6.13 (~OE), J2.17
~Reset: IC6.10 (~MR), IC7.10 (~MR), J2.8
~Serial CP: IC6.11 (SHCP), IC7.11 (SHCP), J2.12

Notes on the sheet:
Green
White
Grey
Yellow

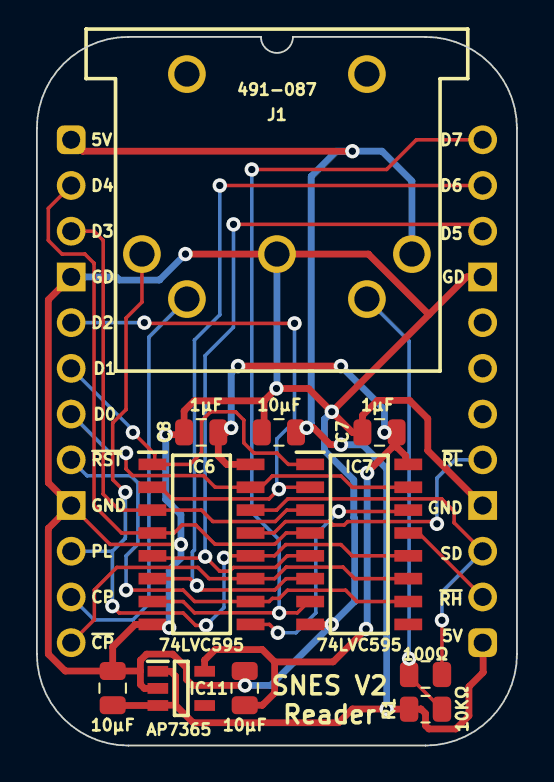
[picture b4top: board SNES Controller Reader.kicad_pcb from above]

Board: 2 copper layers, 26.7 x 39.4 mm, 12 parts (0 on the bottom side), 20 nets.
